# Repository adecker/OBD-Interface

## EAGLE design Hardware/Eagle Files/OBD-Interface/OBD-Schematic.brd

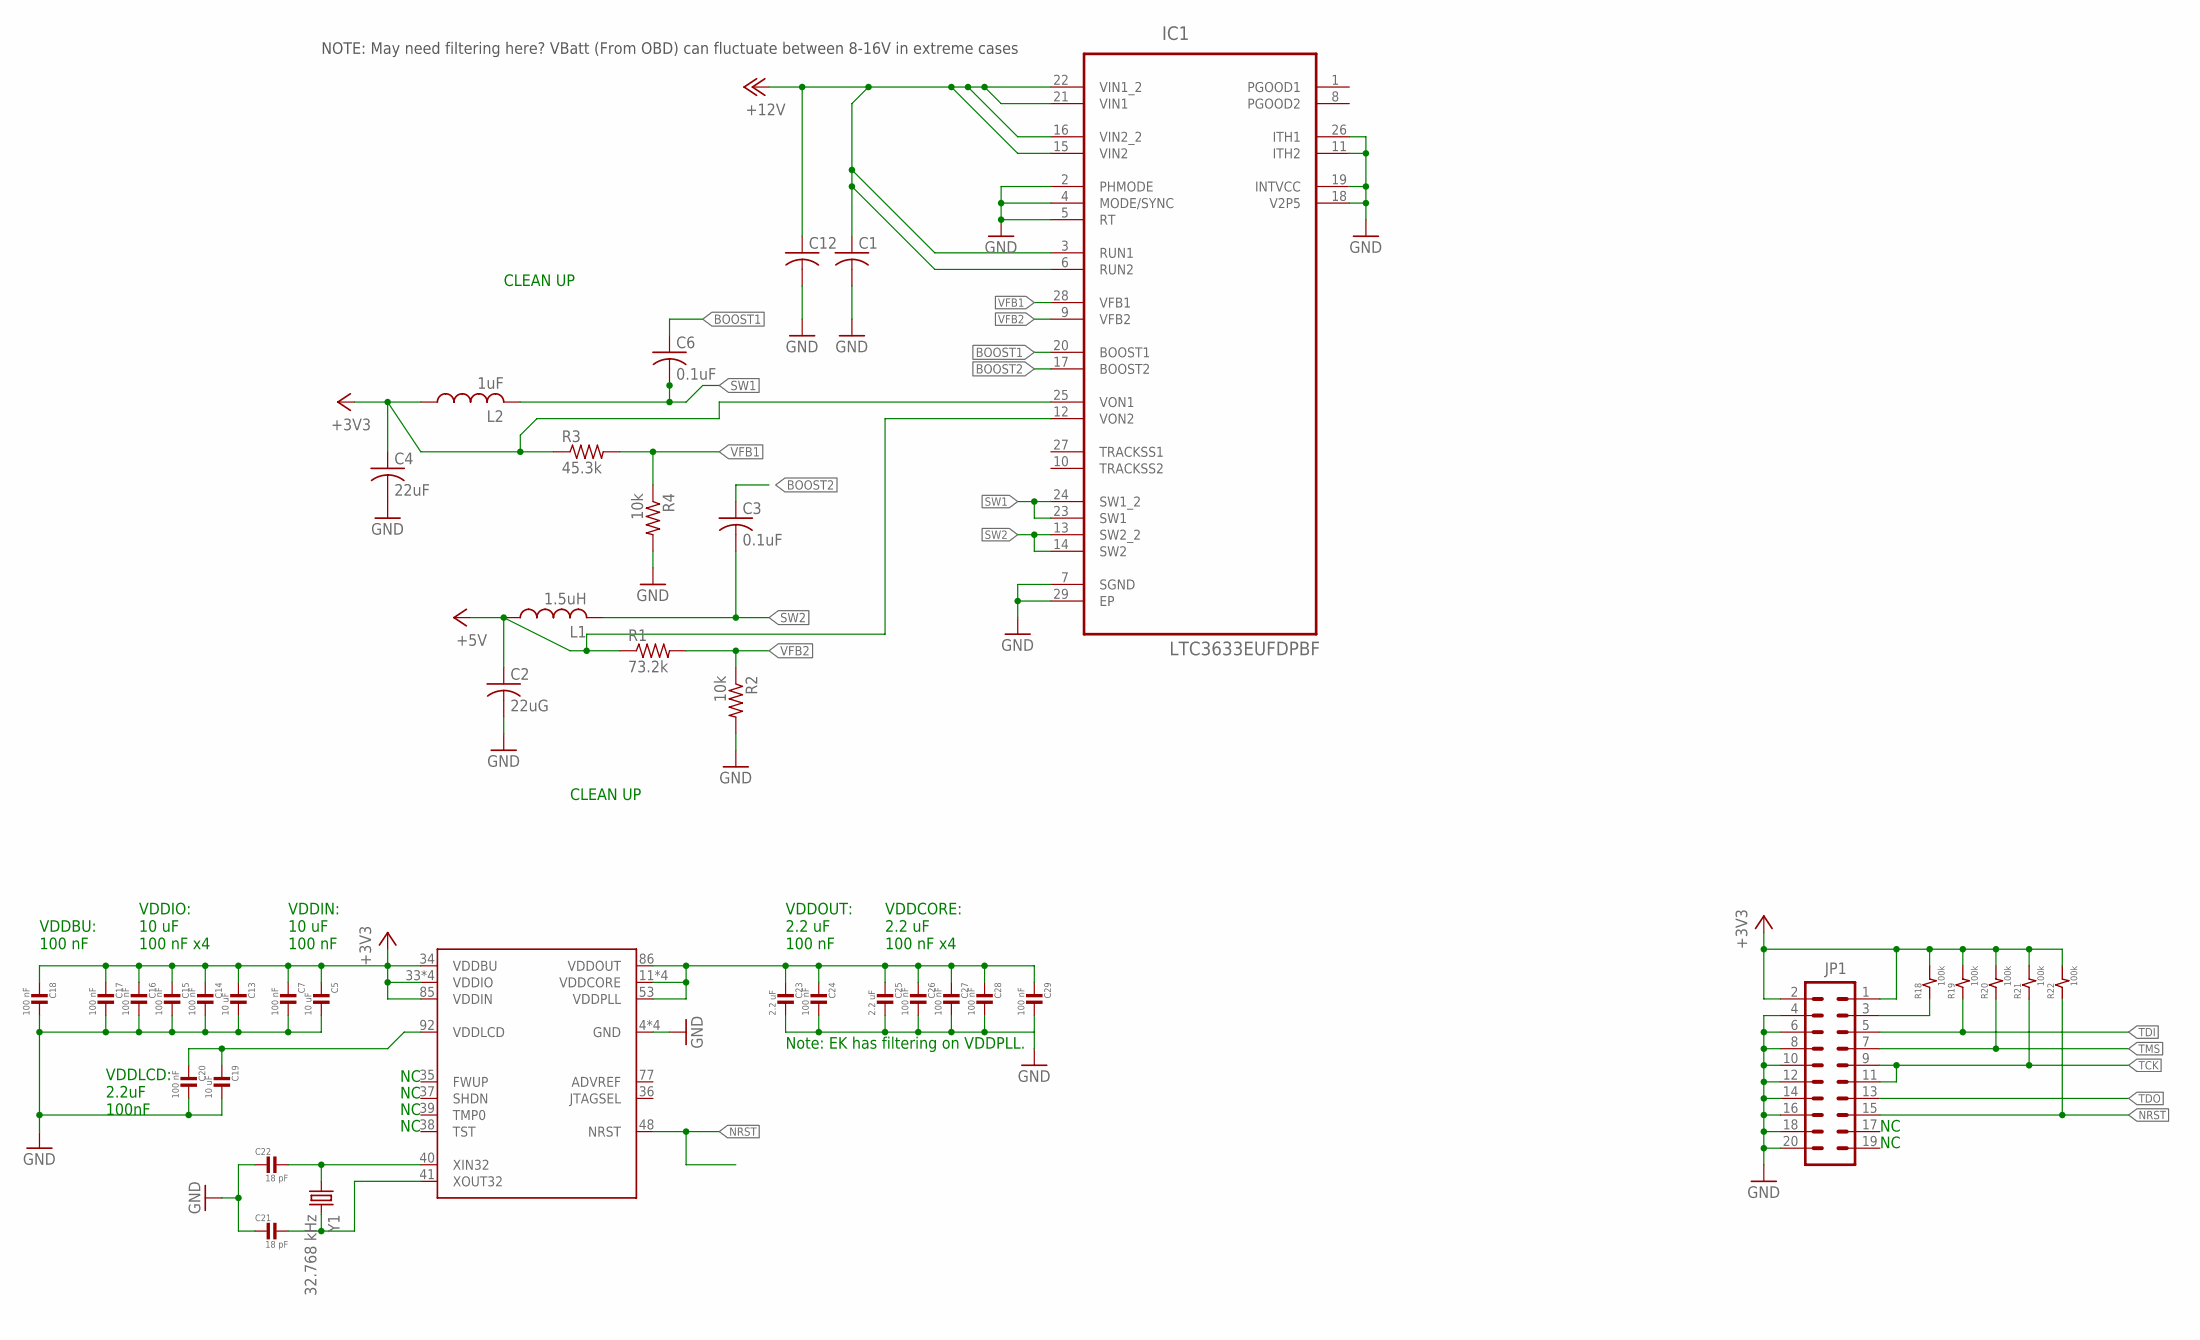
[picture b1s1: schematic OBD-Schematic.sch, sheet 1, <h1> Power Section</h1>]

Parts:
C1, C12: C-USC0805; C0805
C2: 22uG; C0805
C3, C6: 0.1uF; C0805
C4: 22uF; C0805
C5, C13, C19: 10 uF; C0603
C7, C14, C15, C16, C17, C18, C20, C24, C26, C27, C28, C29: 100 nF; C0603
C21, C22: 18 pF; C0603
C23, C25: 2.2 uF; C0603
IC1: LTC3633EUFDPBF; QFN50P400X500X80-29N
JP1: M10X2; 2X10
L1: 1.5uH; L5650M
L2: 1uF; L5650M
R1: 73.2k; R0805
R2, R4: 10k; R0805
R3: 45.3k; R0805
R18, R19, R20, R21, R22: 100k; R0603
U$3: SAM4C32C-100; LQFP-100
Y1: 32.768 kHz; SM49

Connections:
+3V3: C4.1, C5.1, C7.1, C13.1, C14.1, C15.1, C16.1, C17.1, C18.1, IC1.25 (VON1), JP1.1, JP1.2, L2.1, R3.1, R18.2, R19.2, R20.2, R21.2, R22.2, U$3.33 (VDDIO), U$3.34 (VDDBU), U$3.49 (VDDIO), U$3.76 (VDDIO), U$3.85 (VDDIN), U$3.99 (VDDIO); also elsewhere on the board
+5V: C2.1, IC1.12 (VON2), L1.1, R1.1; also elsewhere on the board
BOOST1: C6.1, IC1.20 (BOOST1)
BOOST2: C3.1, IC1.17 (BOOST2)
GND: C1.2, C2.2, C4.2, C5.2, C7.2, C12.2, C13.2, C14.2, C15.2, C16.2, C17.2, C18.2, C19.2, C20.2, C21.1, C22.1, C23.2, C24.2, C25.2, C26.2, C27.2, C28.2, C29.2, IC1.2 (PHMODE), IC1.4 (MODE/SYNC), IC1.5 (RT), IC1.7 (SGND), IC1.11 (ITH2), IC1.18 (V2P5), IC1.19 (INTVCC), IC1.26 (ITH1), IC1.29 (EP), JP1.4, JP1.6, JP1.8, JP1.10, JP1.12, JP1.14, JP1.16, JP1.18, JP1.20, R2.2, R4.2, U$3.4 (GND), U$3.42 (GND), U$3.52 (GND), U$3.78 (GND); also elsewhere on the board
unnamed: JP1.3, R18.1
unnamed: C22.2, U$3.40 (XIN32), Y1.1
unnamed: C21.2, U$3.41 (XOUT32), Y1.2
NRST: JP1.15, R22.1, U$3.48 (NRST)
SW1: C6.2, IC1.23 (SW1), IC1.24 (SW1_2), L2.2
SW2: C3.2, IC1.13 (SW2_2), IC1.14 (SW2), L1.2
TCK: JP1.9, JP1.11, R21.1; also elsewhere on the board
TDI: JP1.5, R19.1; also elsewhere on the board
TDO: JP1.13; also elsewhere on the board
TMS: JP1.7, R20.1; also elsewhere on the board
VDDLCD: C19.1, C20.1, U$3.92 (VDDLCD)
VDDOUT: C23.1, C24.1, C25.1, C26.1, C27.1, C28.1, C29.1, U$3.11 (VDDCORE), U$3.44 (VDDCORE), U$3.53 (VDDPLL), U$3.63 (VDDCORE), U$3.86 (VDDOUT), U$3.89 (VDDCORE)
VFB1: IC1.28 (VFB1), R3.2, R4.1
VFB2: IC1.9 (VFB2), R1.2, R2.1
VIN: C1.1, C12.1, IC1.3 (RUN1), IC1.6 (RUN2), IC1.15 (VIN2), IC1.16 (VIN2_2), IC1.21 (VIN1), IC1.22 (VIN1_2); also elsewhere on the board

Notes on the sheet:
VDDLCD: 2.2uF 100nF
VDDIN: 10 uF 100 nF
VDDOUT: 2.2 uF 100 nF
VDDCORE: 2.2 uF 100 nF x4
VDDIO: 10 uF 100 nF x4
VDDBU: 100 nF
Note: EK has filtering on VDDPLL.
CLEAN UP
NOTE: May need filtering here? VBatt (From OBD) can fluctuate between 8-16V in extreme cases

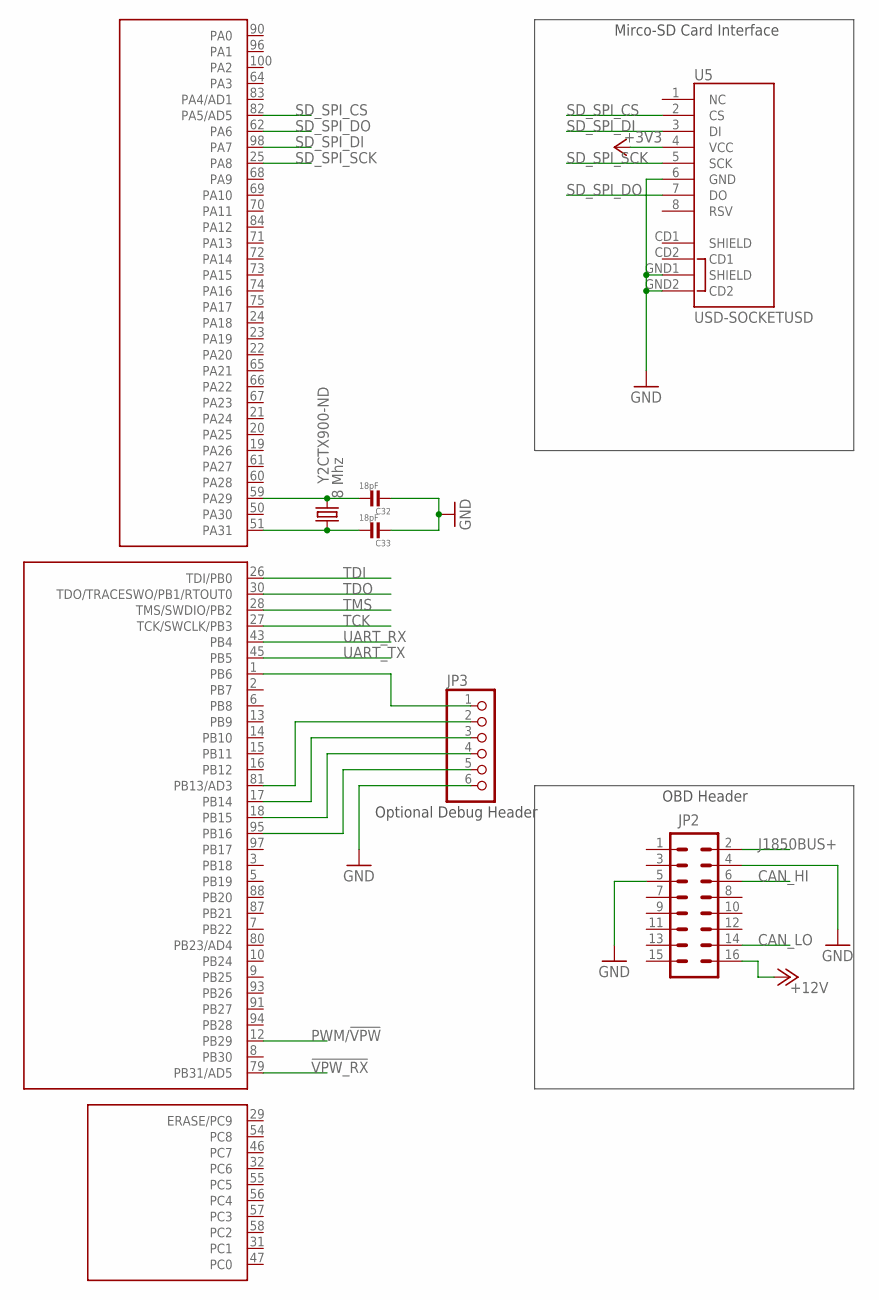
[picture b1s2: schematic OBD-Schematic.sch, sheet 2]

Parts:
C32, C33: 18pF; C0603
JP2: M08X2; 2X8
JP3: PINHD-1X6CLEAN; 1X06-CLEAN
U5: USD-SOCKETUSD; USD-SOCKET-PP
U$3: SAM4C32C-100; LQFP-100
Y2CTX900-ND: 8 Mhz; HC49US

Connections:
!VPW_RX: U$3.79 (PB31/AD5); also elsewhere on the board
+3V3: U5.4 (VCC); also elsewhere on the board
CAN_HI: JP2.6; also elsewhere on the board
CAN_LO: JP2.14; also elsewhere on the board
GND: C32.1, C33.1, JP2.4, JP2.5, JP3.6, U5.6 (GND), U5.GND1 (SHIELD), U5.GND2 (CD2); also elsewhere on the board
J1850BUS+: JP2.2; also elsewhere on the board
unnamed: C33.2, U$3.51 (PA31), Y2CTX900-ND.1
unnamed: C32.2, U$3.59 (PA29), Y2CTX900-ND.2
unnamed: JP3.1, U$3.1 (PB6)
unnamed: JP3.2, U$3.81 (PB13/AD3)
unnamed: JP3.3, U$3.17 (PB14)
unnamed: JP3.4, U$3.18 (PB15)
unnamed: JP3.5, U$3.95 (PB16)
PWM/!VPW: U$3.12 (PB29); also elsewhere on the board
SD_SPI_CS: U5.2 (CS), U$3.82 (PA5/AD5)
SD_SPI_DI: U5.3 (DI), U$3.98 (PA7)
SD_SPI_DO: U5.7 (DO), U$3.62 (PA6)
SD_SPI_SCK: U5.5 (SCK), U$3.25 (PA8)
TCK: U$3.27 (TCK/SWCLK/PB3); also elsewhere on the board
TDI: U$3.26 (TDI/PB0); also elsewhere on the board
TDO: U$3.30 (TDO/TRACESWO/PB1/RTOUT0); also elsewhere on the board
TMS: U$3.28 (TMS/SWDIO/PB2); also elsewhere on the board
UART_RX: U$3.43 (PB4); also elsewhere on the board
UART_TX: U$3.45 (PB5); also elsewhere on the board
VIN: JP2.16; also elsewhere on the board

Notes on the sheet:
Mirco-SD Card Interface
OBD Header
Optional Debug Header

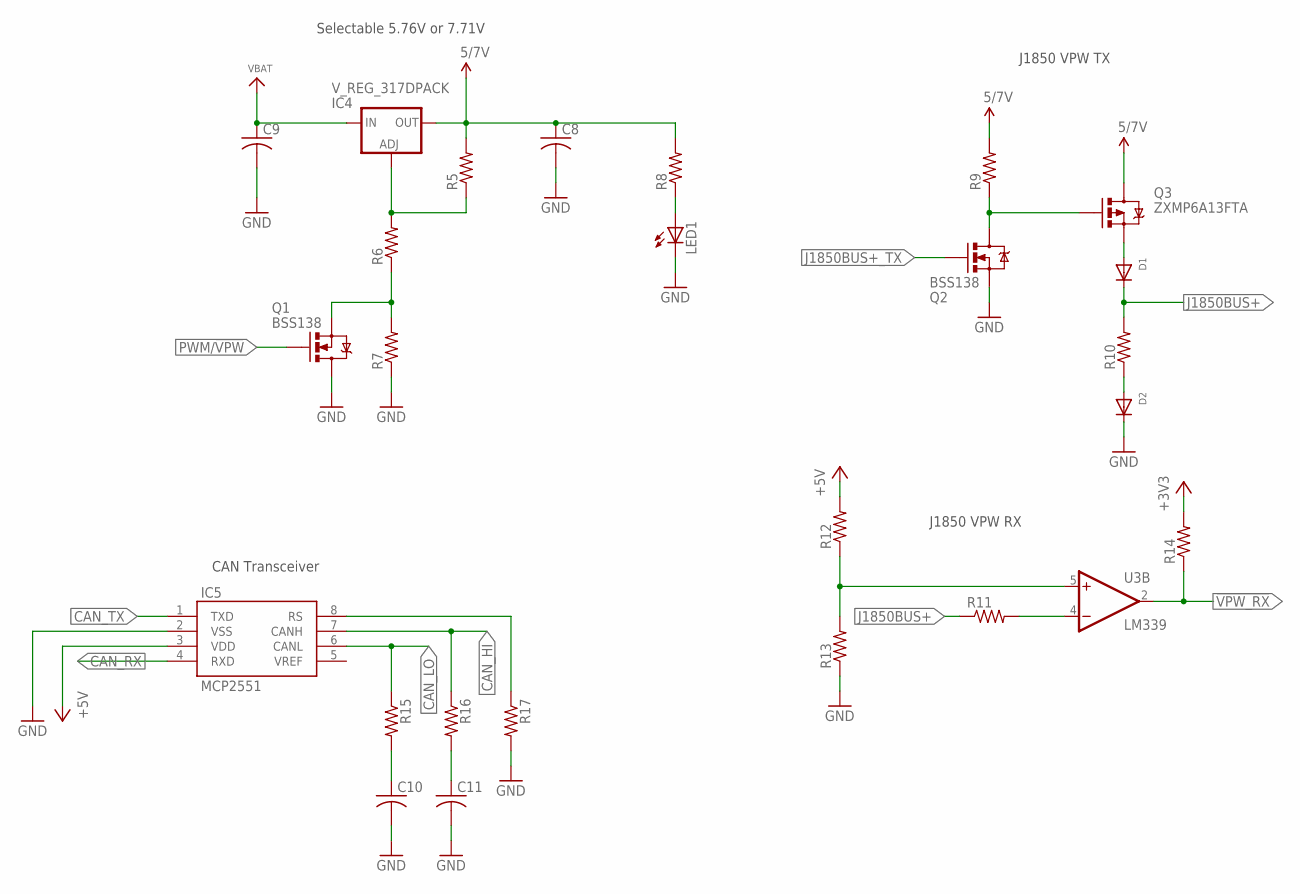
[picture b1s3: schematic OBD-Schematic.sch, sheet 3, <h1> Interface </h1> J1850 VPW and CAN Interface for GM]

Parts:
C8, C9, C10, C11: C-USC0805; C0805
D1, D2: DIODESOT23_REFLOW; SOT23-R
IC4: V_REG_317DPACK; V-REG_DPACK
IC5: MCP2551; SO08
LED1: LEDCHIP-LED0805; CHIP-LED0805
Q1, Q2: BSS138; SOT23-3
Q3: ZXMP6A13FTA; SOT23-3
R5, R6, R7, R8, R9, R10, R11, R12, R13, R14, R15, R16, R17: R-US_R0805; R0805
U3: LM339; TSSOP-14

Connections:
5/7V: C8.1, IC4.4 (OUT), Q3.3 (D), R5.2, R8.2, R9.2
!VPW_RX: R14.1, U3.2 (OUT); also elsewhere on the board
+3V3: R14.2; also elsewhere on the board
+5V: IC5.3 (VDD), R12.2; also elsewhere on the board
CAN_HI: IC5.7 (CANH), R16.1; also elsewhere on the board
CAN_LO: IC5.6 (CANL), R15.1; also elsewhere on the board
CAN_RX: IC5.4 (RXD)
CAN_TX: IC5.1 (TXD)
GND: C8.2, C9.2, C10.2, C11.2, D2.3 (C), IC5.2 (VSS), LED1.C, Q1.3 (D), Q2.2 (S), R7.1, R13.1, R17.2, U3.12 (GND); also elsewhere on the board
J1850BUS+: D1.3 (C), R10.2, R11.1; also elsewhere on the board
J1850BUS+_TX: Q2.1 (G)
unnamed: Q1.2 (S), R6.1, R7.2
unnamed: IC5.8 (RS), R17.1
unnamed: R12.1, R13.2, U3.5 (+IN)
unnamed: Q2.3 (D), Q3.1 (G), R9.1
unnamed: IC4.1 (ADJ), R5.1, R6.2
unnamed: D1.1 (A), Q3.2 (S)
unnamed: R11.2, U3.4 (-IN)
unnamed: D2.1 (A), R10.1
unnamed: LED1.A, R8.1
unnamed: C10.1, R15.2
unnamed: C11.1, R16.2
PWM/!VPW: Q1.1 (G); also elsewhere on the board
VCC: U3.3 (VCC)
VIN: C9.1, IC4.3 (IN); also elsewhere on the board

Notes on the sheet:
Selectable 5.76V or 7.71V
J1850 VPW TX
CAN Transceiver
J1850 VPW RX

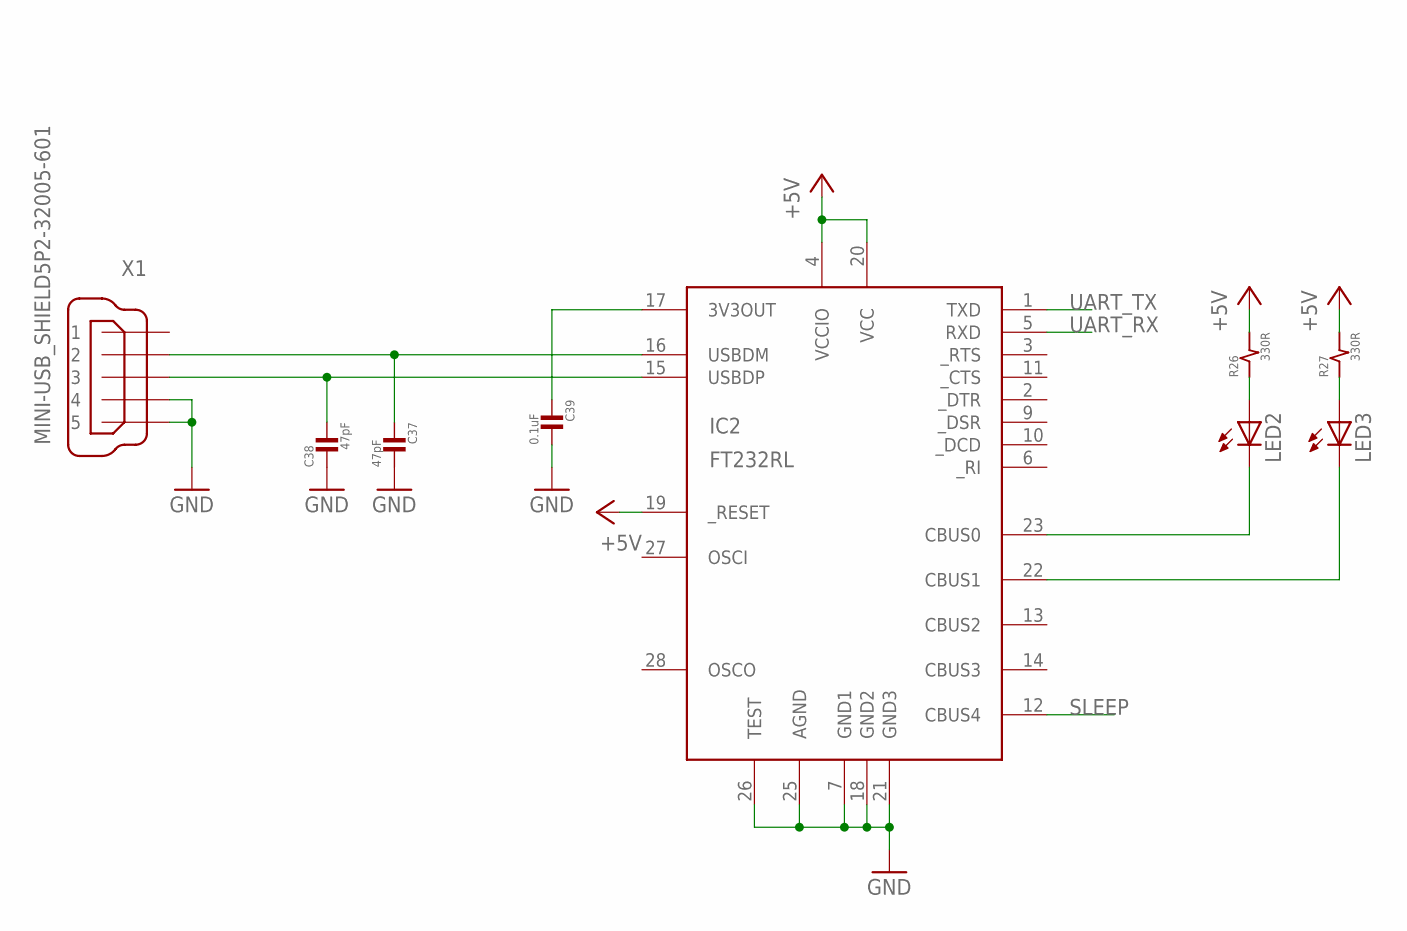
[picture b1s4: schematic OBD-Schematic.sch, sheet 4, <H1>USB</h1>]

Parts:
C37, C38: 47pF; C0603
C39: 0.1uF; C0603
IC2: FT232RL; SSOP28DB
LED2, LED3: LEDCHIPLED_0805; CHIPLED_0805
R26, R27: 330R; R0603
X1: MINI-USB_SHIELD5P2-32005-601; 32005-601

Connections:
+5V: IC2.4 (VCCIO), IC2.19 (_RESET), IC2.20 (VCC), R26.2, R27.2; also elsewhere on the board
GND: C37.2, C38.1, C39.2, IC2.7 (GND1), IC2.18 (GND2), IC2.21 (GND3), IC2.25 (AGND), IC2.26 (TEST), X1.4, X1.5; also elsewhere on the board
unnamed: C37.1, IC2.16 (USBDM), X1.2
unnamed: C38.2, IC2.15 (USBDP), X1.3
unnamed: LED2.A, R26.1
unnamed: LED3.A, R27.1
unnamed: IC2.23 (CBUS0), LED2.C
unnamed: IC2.22 (CBUS1), LED3.C
unnamed: C39.1, IC2.17 (3V3OUT)
SLEEP: IC2.12 (CBUS4)
UART_RX: IC2.5 (RXD); also elsewhere on the board
UART_TX: IC2.1 (TXD); also elsewhere on the board

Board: 4 copper layers, 81 parts (0 on the bottom side), 57 nets, no tracks yet.

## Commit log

2015-10-02 Initial
    Added Schematic Files and common libraries.
2015-10-03 LTC3633 Wired Up
    Added the LTC3633 Buck switching PSU.
2015-10-03 Added Examples
2015-10-03 J1850VPW Interface hardware
    Hardware to interface between the micro and the bus laid. Needs to be
    valued.
2015-10-03 CAN Transceiver Added
    Everything needs to be valued. This completes the GM side of the
    transceiver. v1 will only talk to GM. This is where the market is
    currently and I know the most about. Future revisions will add support
    for ISO and J1850 PWM
2015-10-04 Update project file
2015-10-06 Removed Eagle's "backup" files and added them to .gitignore
2015-10-06 Added passives library to get placeholders for R and C components.
2015-10-06 Added a library to hold the custom parts we use (like the SAM4C).
2015-10-06 Added the SAM4C (in the 144-pin package) to the schematic and started hooking it up.
2015-10-06 Added OBD header and uSD Card slot
2015-10-07 Added Flash and 8Mhz oscillator
2015-10-09 Added USB, Debug Header, Added Board File.
2015-10-16 Started Layout - Pushing incase of act of God
    Like fire, lighting strike, armageddon
2015-10-16 More

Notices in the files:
parts and their libraries:
SparkFun-PowerIC: Licensing: Creative Commons ShareAlike 4.0 International - https://creativecommons.org/licenses/by-sa/4.0
microbuilder: This work is placed in the public domain, and may be freely used for commercial and non-commercial work with the following conditions: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
